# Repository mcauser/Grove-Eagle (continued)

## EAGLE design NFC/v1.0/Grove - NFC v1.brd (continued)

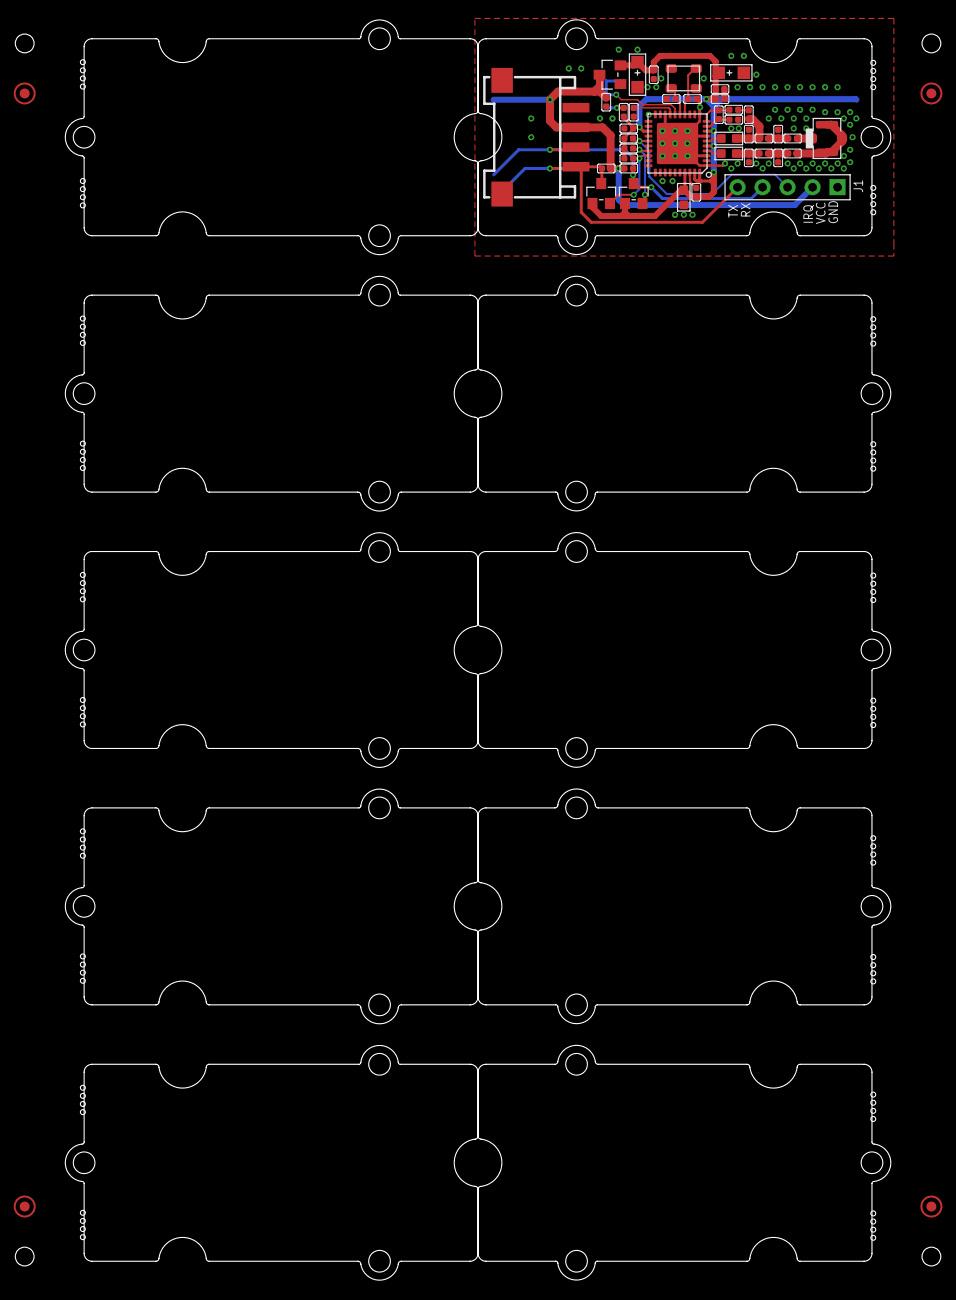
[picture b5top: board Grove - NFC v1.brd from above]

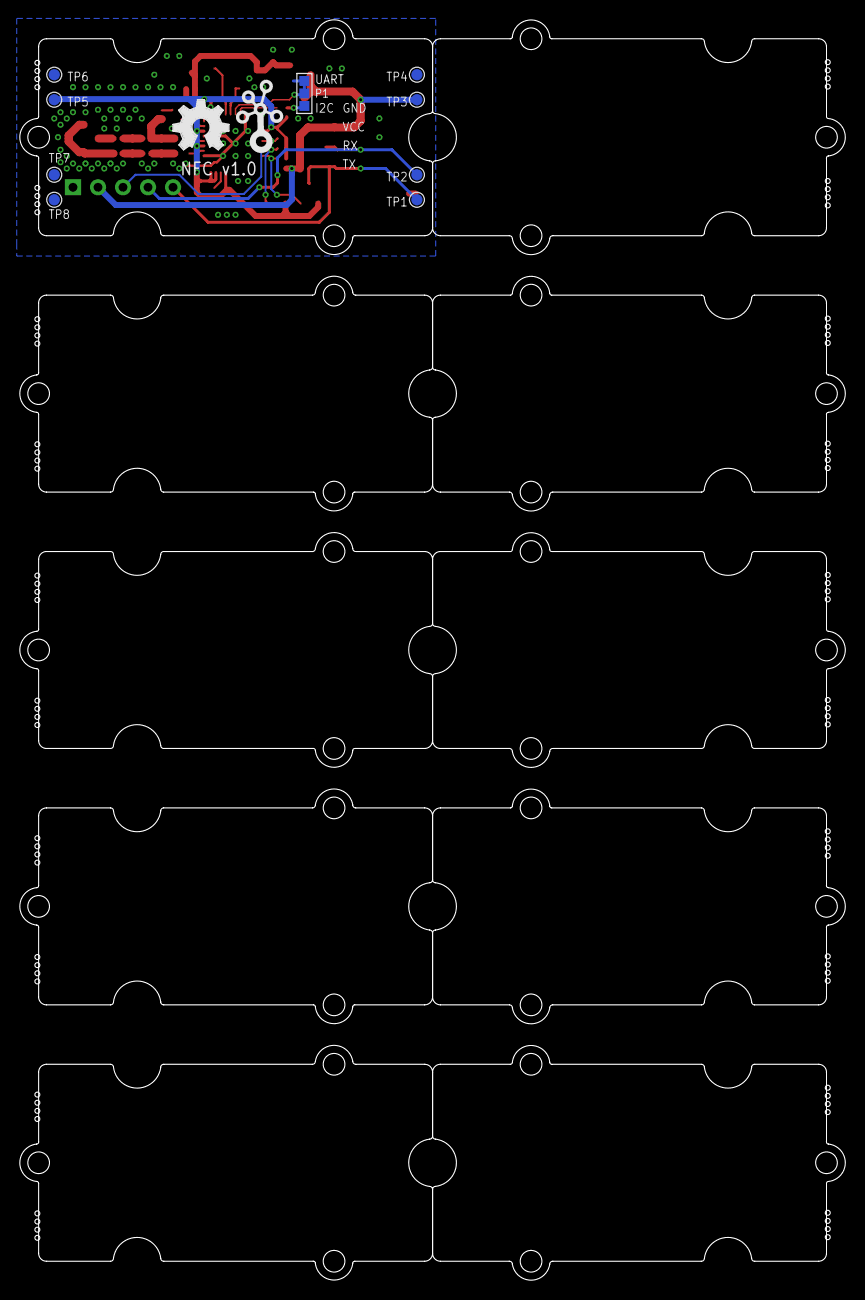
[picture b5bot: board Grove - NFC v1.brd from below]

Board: 2 copper layers, 83.8 x 128.0 mm, 65 parts (11 on the bottom side), 25 nets.

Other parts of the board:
U$2, U$5, U$6, U$7, U$8, U$9, U$10, U$11, U$12, U$13: GROVE-TEST-PLATFORM
U$3: OSHW_FILLX200_NOTEXT
U$4: TWIGLOGO

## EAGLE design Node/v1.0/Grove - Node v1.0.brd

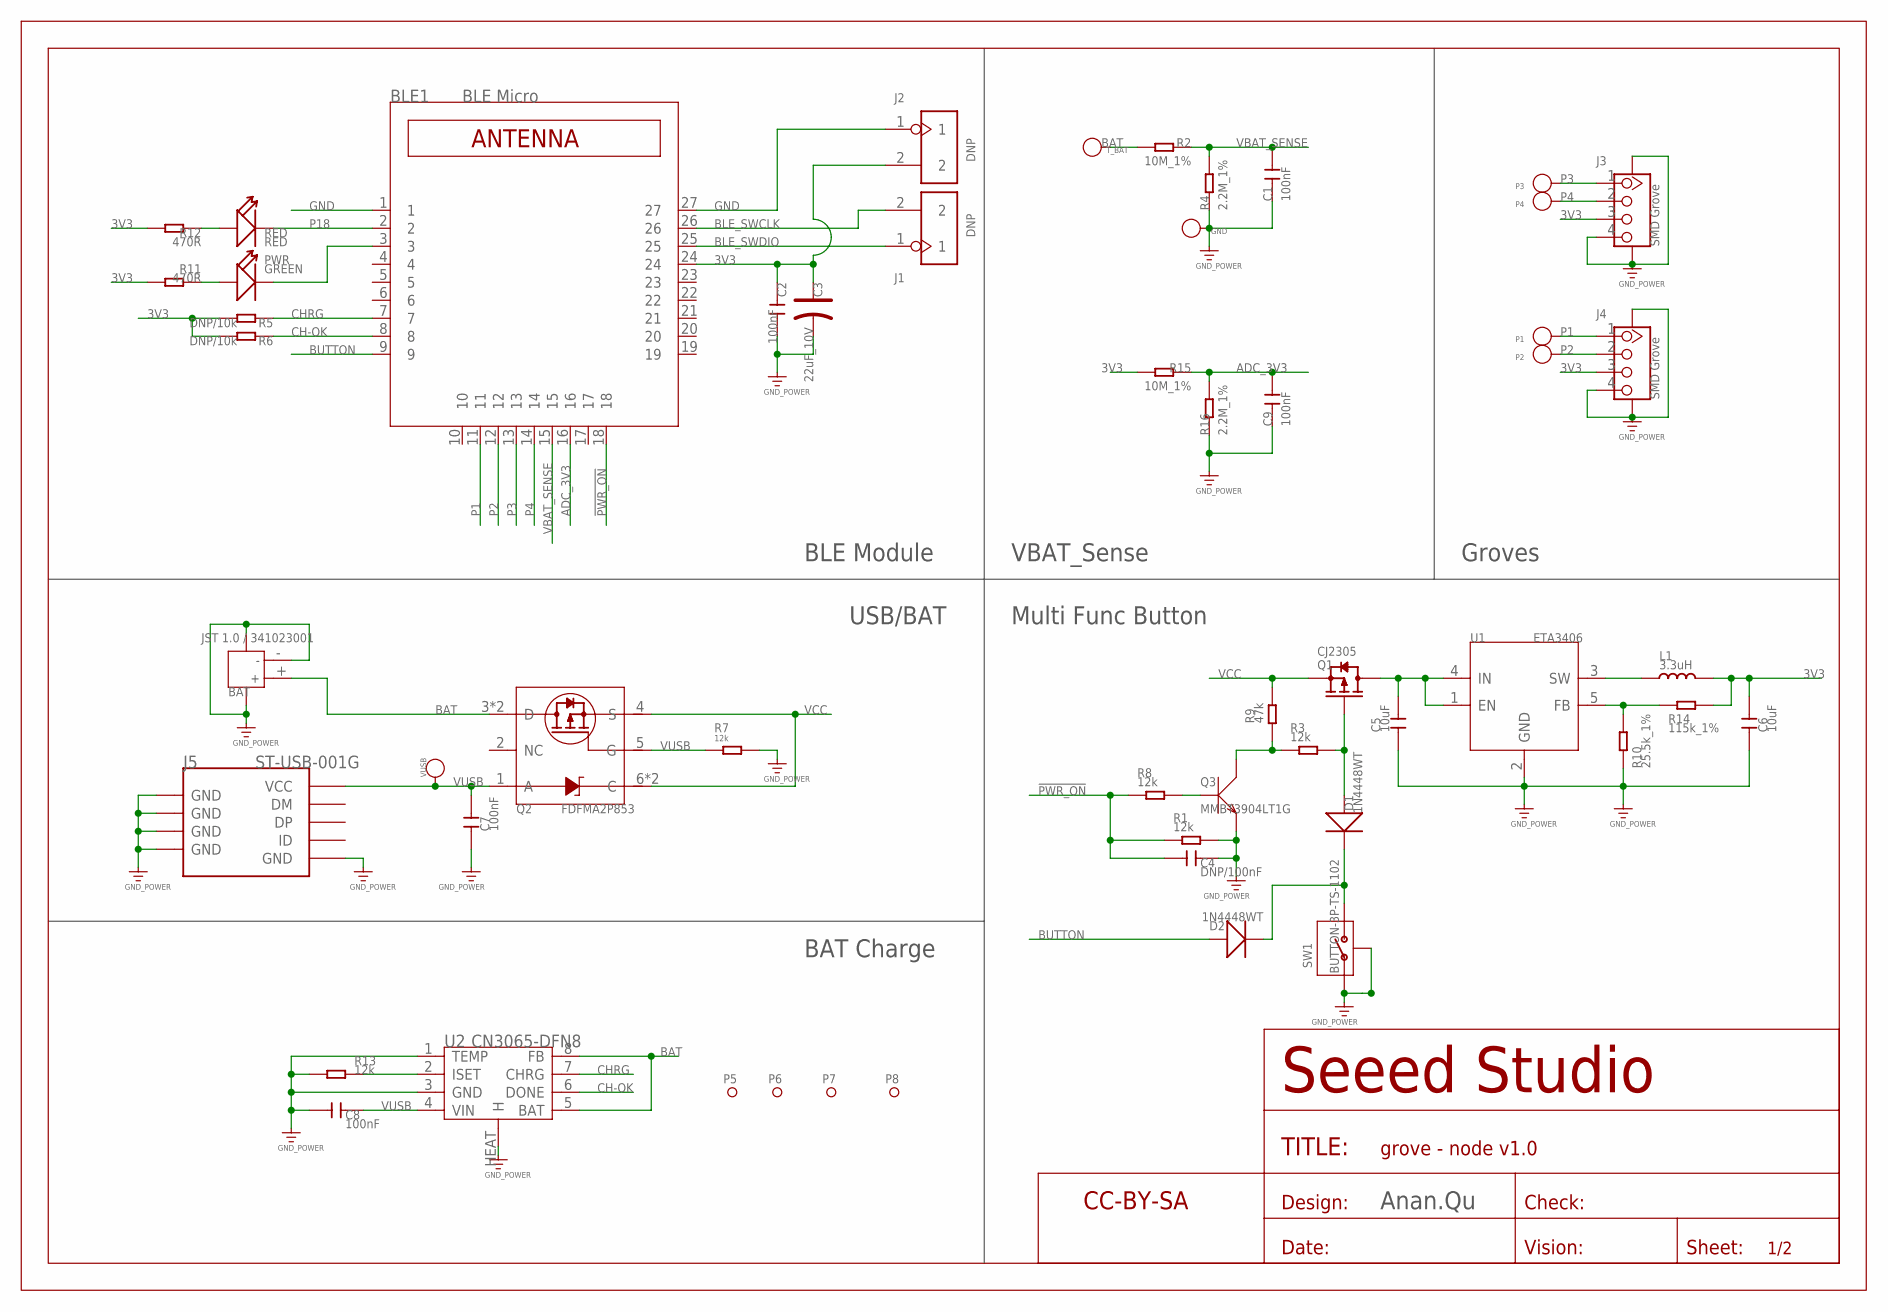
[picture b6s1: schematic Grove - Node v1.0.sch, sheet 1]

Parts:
BAT: JST 1.0 / 341023001; JST-SMD-2P-1.0-90D
BLE1: BLE Micro; SEEED_BLE_MODULE_PAD
C1, C2, C7, C8, C9: 100nF; C0402
C3: 22uF_10V; AVX-A
C4: DNP/100nF; C0402
C5, C6: 10uF; C0805
D1, D2: 1N4448WT; SOD523
GND: PAD-TEST-POINT'4545'; TP_4545
J1, J2: DNP; 2P-2.0-55/32MIL
J3, J4: SMD Grove; 4P-SMD-2.0
J5: ST-USB-001G; MICRO-USB
L1: 3.3uH; L3015
P1, P2, P3, P4: PAD-TEST-POINT'4545'; TP_4545
P5, P6, P7, P8: PAD-MARK'ANNULAR'; ROUND-MARK-1.0
PWR: GREEN; LED-0402
Q1: CJ2305; SOT23
Q2: FDFMA2P853; 6P-SMD-W/-HEAT
Q3: MMBT3904LT1G; SOT-23
R1, R3, R7, R8, R13: 12k; R0402
R2, R15: 10M_1%; R0402
R4, R16: 2.2M_1%; R0402
R5, R6: DNP/10k; R0402
R9: 47k; R0402
R10: 25.5k_1%; R0402
R11, R12: 470R; R0402
R14: 115k_1%; R0402
RED: RED; LED-0402
SW1: BUTTON-3P-TS-1102; 3P-1.5-L4.5*W2.9*H4.5-2.8MM
T_BAT: PAD-TEST-POINT'4545'; TP_4545
U1: ETA3406; SOT23-5
U2: CN3065-DFN8; DFN8
U$4: SEEEDSTUDIO-OPEN-SCH-FRAME; SEEEDSTUDIO-PCB-FRAME
VUSB: PAD-TEST-POINT'4545'; TP_4545

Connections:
3V3: BLE1.24, C2.1, C3.+, C6.2, J2.2, J3.3, J4.3, L1.2, R5.2, R6.2, R11.2, R12.2, R14.1, R15.2
!PWR_ON: BLE1.18, C4.1, R1.2, R8.2
ADC_3V3: BLE1.16, C9.1, R15.1, R16.2
BAT: BAT.+ (1), Q2.3 (D), Q2.P2 (D), R2.2, T_BAT.T, U2.5 (BAT), U2.8 (FB)
BLE_SWCLK: BLE1.26, J1.2
BLE_SWDIO: BLE1.25, J1.1
BUTTON: BLE1.9, D2.+
CH-OK: BLE1.8, R6.1, U2.6 (DONE)
CHRG: BLE1.7, R5.1, U2.7 (CHRG)
GND: BAT.3, BAT.4, BAT.- (2), BLE1.1, BLE1.27, C1.2, C2.2, C3.-, C4.2, C5.1, C6.1, C7.1, C8.1, C9.2, GND.T, J2.1, J3.4, J3.SS1, J3.SS2, J4.4, J4.SS1, J4.SS2, J5.5 (GND), J5.S1 (GND), J5.S2 (GND), J5.S3 (GND), J5.S4 (GND), J5.S5 (GND), J5.S6 (GND), Q3.2 (E), R1.1, R4.1, R7.2, R10.2, R13.1, R16.1, SW1.1, SW1.3 (GND), U1.2 (GND), U2.1 (TEMP), U2.3 (GND), U2.HEAT (H)
ISET: R13.2, U2.2 (ISET)
unnamed: PWR.+, R11.1
unnamed: R12.1, RED.+
unnamed: L1.1, U1.3 (SW)
unnamed: R10.1, R14.2, U1.5 (FB)
unnamed: Q3.3 (C), R3.2, R9.1
unnamed: D1.-, D2.-, SW1.2
unnamed: Q3.1 (B), R8.1
unnamed: C5.2, Q1.3 (D), U1.1 (EN), U1.4 (IN)
unnamed: D1.+, Q1.1 (G), R3.1
P1: BLE1.11, J4.1, P1.T
P2: BLE1.12, J4.2, P2.T
P3: BLE1.13, J3.1, P3.T
P4: BLE1.14, J3.2, P4.T
P5: BLE1.3, PWR.-
P18: BLE1.2, RED.-
VBAT_SENSE: BLE1.15, C1.1, R2.1, R4.2
VCC: Q1.2 (S), Q2.4 (S), Q2.6 (C), Q2.P1 (C), R9.2
VUSB: C7.2, C8.2, J5.1 (VCC), Q2.1 (A), Q2.5 (G), R7.1, U2.4 (VIN), VUSB.T

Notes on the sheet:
BLE Module
VBAT_Sense
USB/BAT
Multi Func Button
Groves
BAT Charge
Anan.Qu

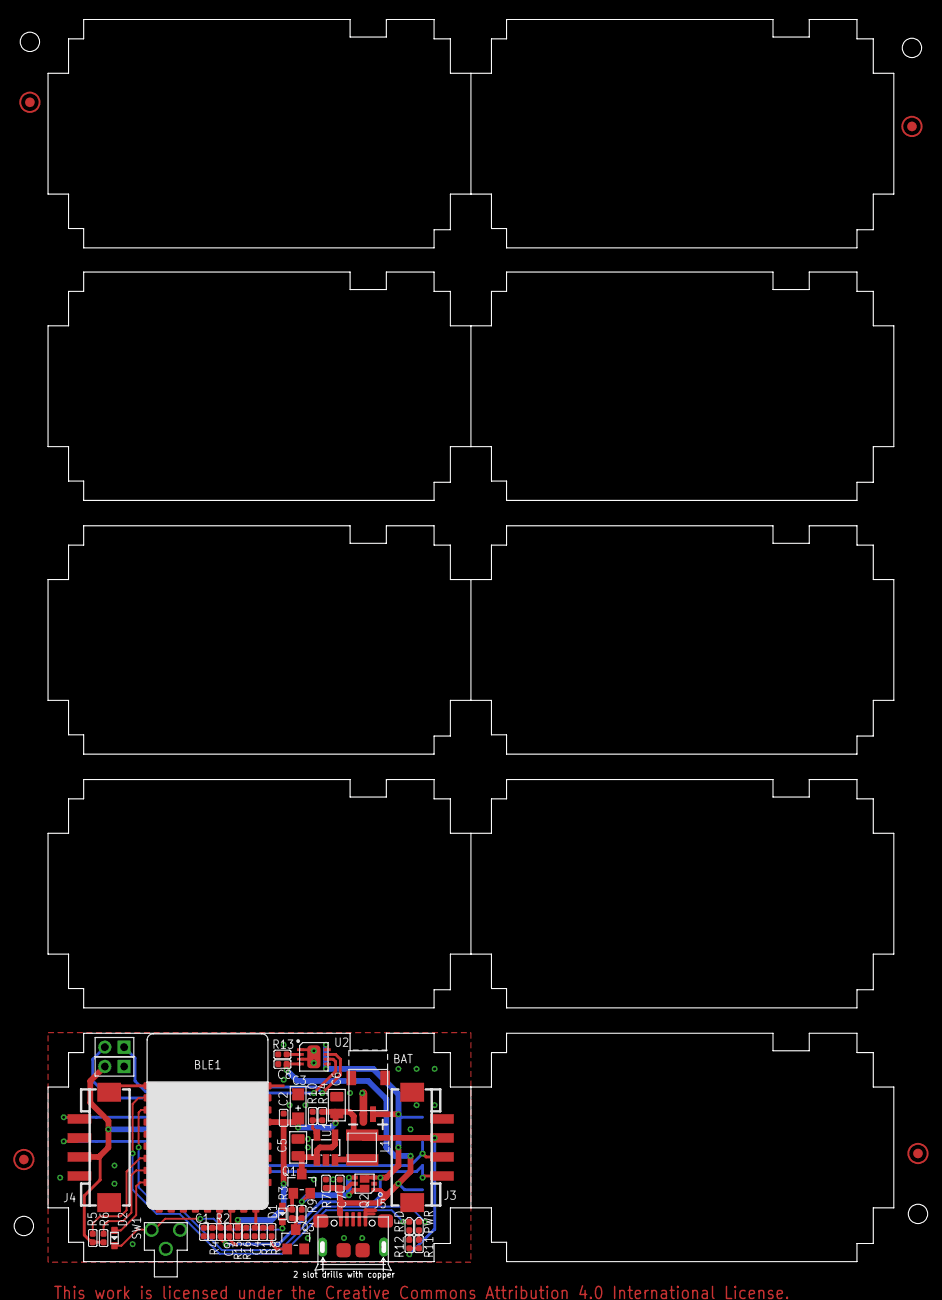
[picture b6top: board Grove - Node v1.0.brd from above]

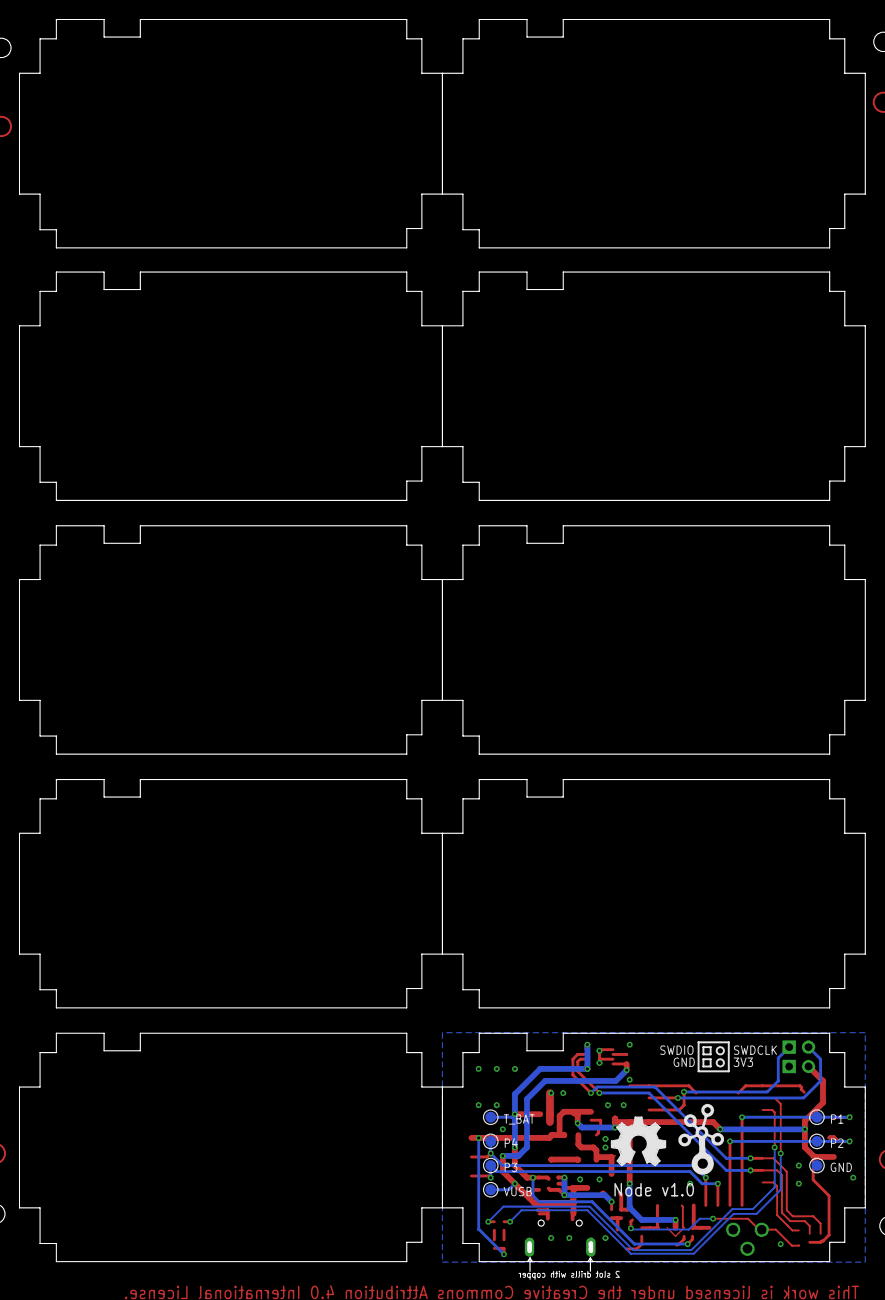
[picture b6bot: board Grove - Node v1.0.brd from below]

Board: 2 copper layers, 88.9 x 131.6 mm, 57 parts (9 on the bottom side), 29 nets.

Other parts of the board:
U$2: OSHW_FILLX200_NOTEXT
U$3: TWIGLOGO

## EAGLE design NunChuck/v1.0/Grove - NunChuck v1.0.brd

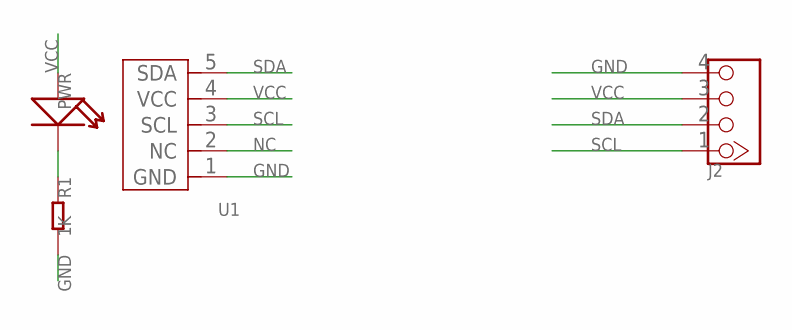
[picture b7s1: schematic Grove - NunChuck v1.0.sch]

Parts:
J2: TWIG-4P-2.0-2.0; 4P-2.0
PWR: LED'0603'; LED-0603
R1: 1K; R0603
U1: WIICHUCK

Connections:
GND: J2.4, R1.2, U1.1 (GND)
unnamed: PWR.-, R1.1
NC: U1.2 (NC)
SCL: J2.1, U1.3 (SCL)
SDA: J2.2, U1.5 (SDA)
VCC: J2.3, PWR.+, U1.4 (VCC)

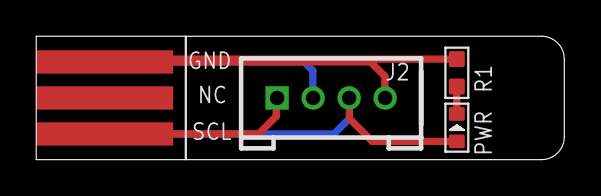
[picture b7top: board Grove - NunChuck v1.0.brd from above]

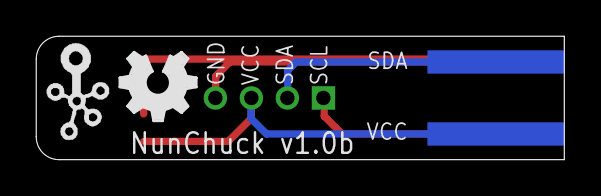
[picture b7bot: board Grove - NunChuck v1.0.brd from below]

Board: 2 copper layers, 29.3 x 6.9 mm, 6 parts (2 on the bottom side), 5 nets.

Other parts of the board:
U$5: TWIGLOGO_SMALL
U$6: OSHW_FILLX150_NOTEXT
